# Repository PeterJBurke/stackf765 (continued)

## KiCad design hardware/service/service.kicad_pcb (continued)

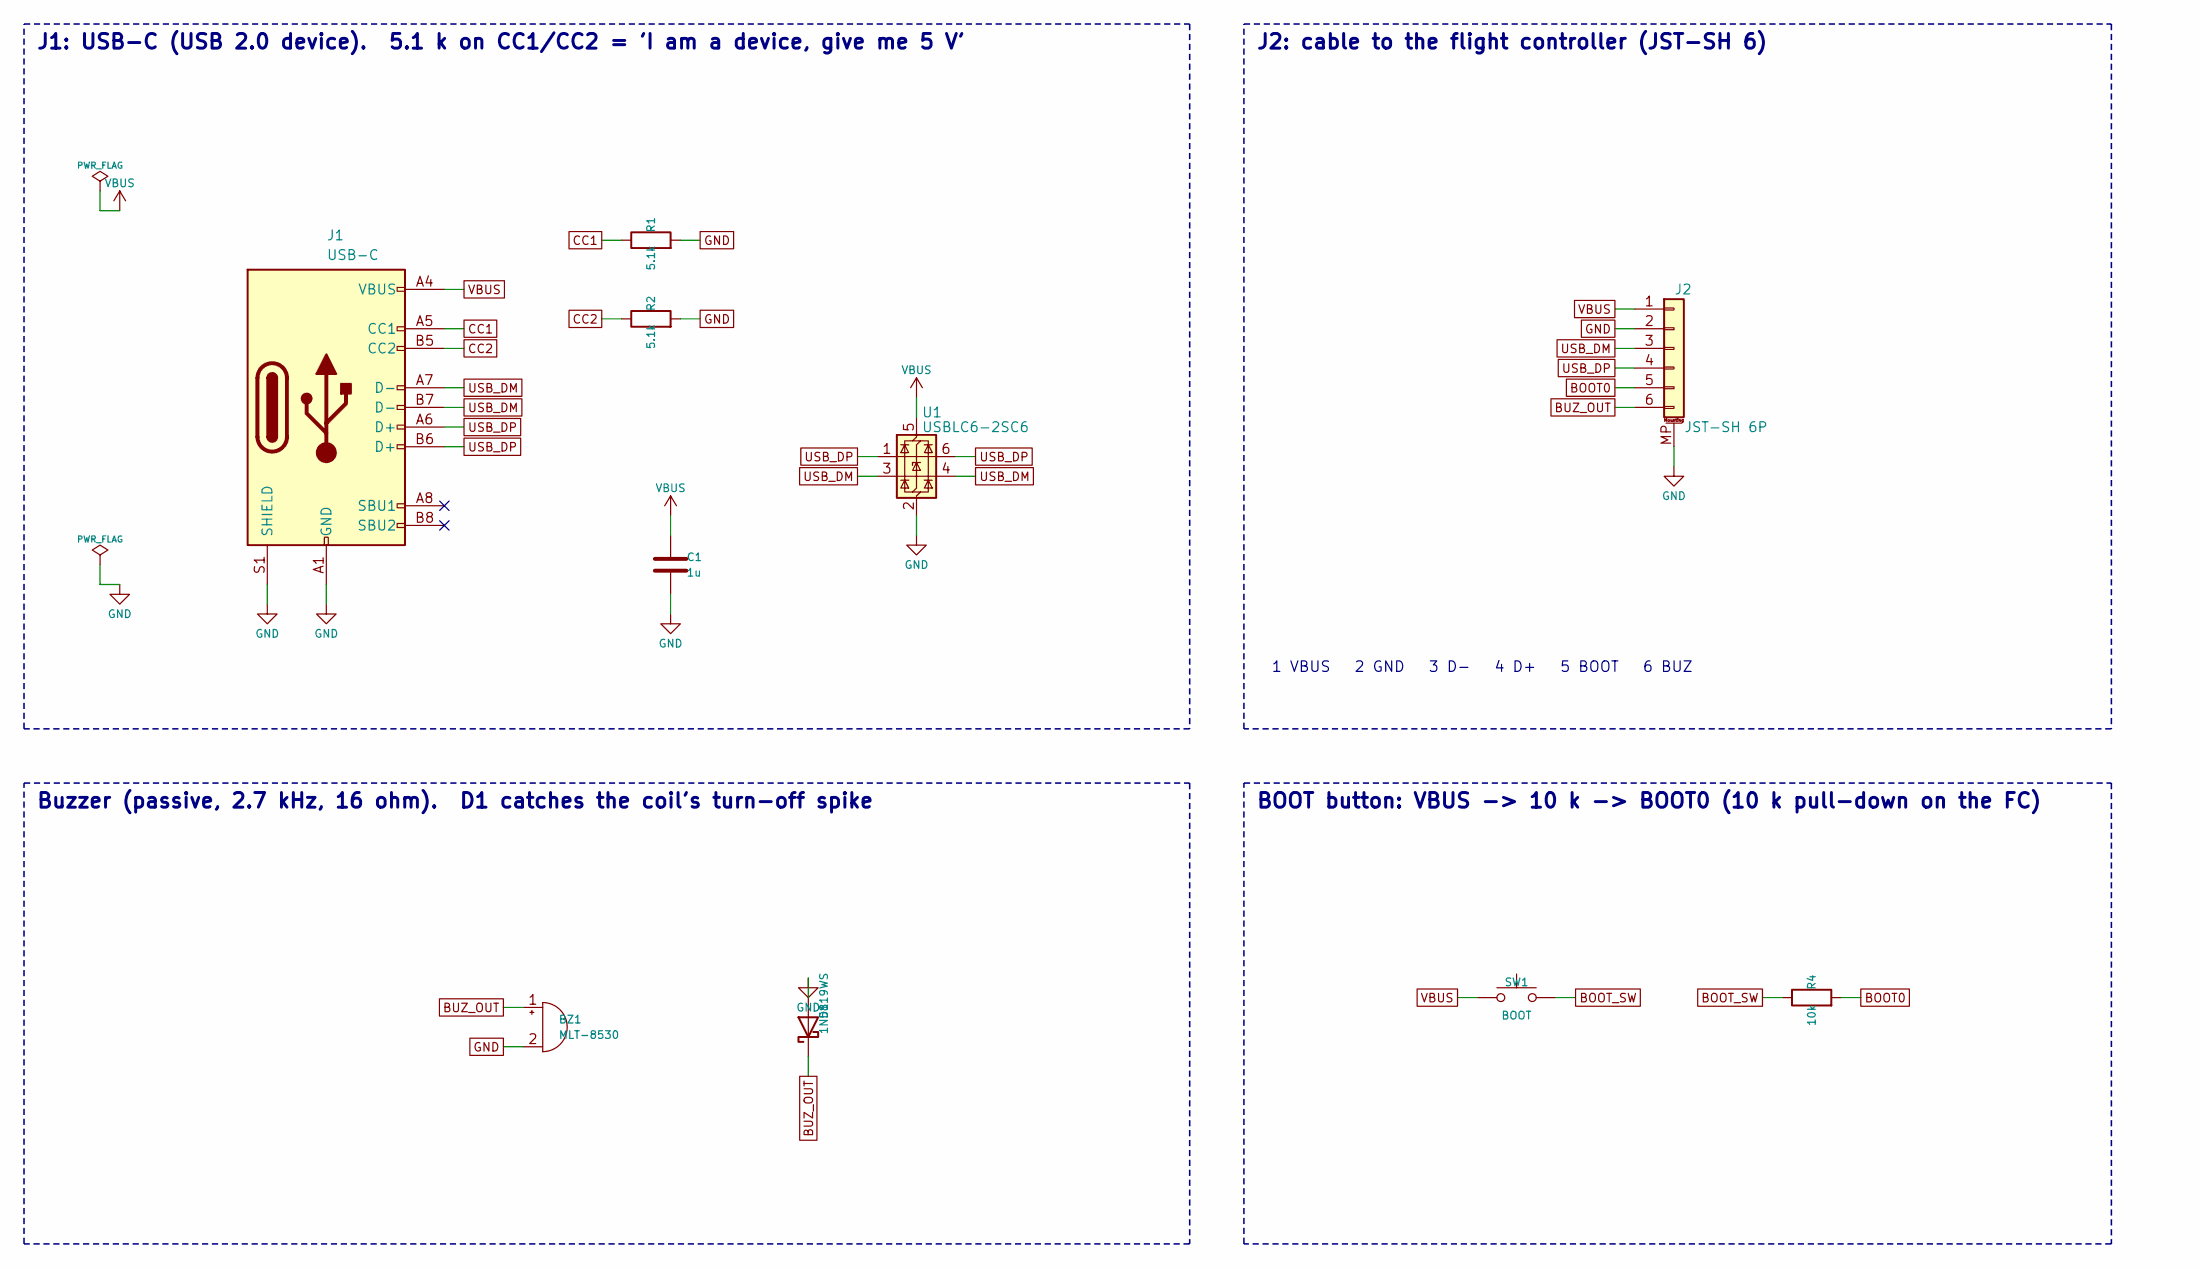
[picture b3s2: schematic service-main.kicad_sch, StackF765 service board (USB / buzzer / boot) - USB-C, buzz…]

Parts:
BZ1: MLT-8530; MagneticBuzzer_CUI_CMT-8504-100-SMT; MPN MLT-8530; LCSC C94599
C1: 1u; C_0402_1005Metric; MPN CL05A105KA5NQNC; LCSC C52923
D1: 1N5819WS; D_SOD-323; MPN 1N5819WS; LCSC C191023
J1: USB-C; USB_C_Receptacle_HRO_TYPE-C-31-M-12; MPN TYPE-C-31-M-12; LCSC C165948
J2: JST-SH 6P; JST_SH_SM06B-SRSS-TB_1x06-1MP_P1.00mm_Horizontal; MPN SM06B-SRSS-TB(LF)(SN); LCSC C160405
R1, R2: 5.1k; R_0402_1005Metric; MPN 0402WGF5101TCE; LCSC C25905
R4: 10k; R_0402_1005Metric; MPN 0402WGF1002TCE; LCSC C25744
SW1: BOOT; SW_Push_1P1T_XKB_TS-1187A; MPN TS-1187A-B-A-B; LCSC C318884
U1: USBLC6-2SC6; SOT-23-6; MPN USBLC6-2SC6; LCSC C7519

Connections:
BOOT0: J2.5, R4.2
BOOT_SW: R4.1, SW1.2
BUZ_OUT: BZ1.1 (+), D1.1 (K), J2.6
CC1: J1.A5 (CC1), R1.1
CC2: J1.B5 (CC2), R2.1
GND: BZ1.2 (-), C1.2, D1.2 (A), J1.A1 (GND), J1.A12 (GND), J1.B1 (GND), J1.B12 (GND), J1.S1 (SHIELD), J2.2, J2.MP (MountPin), R1.2, R2.2, U1.2 (GND)
USB_DM: J1.A7 (D-), J1.B7 (D-), J2.3, U1.3 (I/O2), U1.4 (I/O2)
USB_DP: J1.A6 (D+), J1.B6 (D+), J2.4, U1.1 (I/O1), U1.6 (I/O1)
VBUS: C1.1, J1.A4 (VBUS), J1.A9 (VBUS), J1.B4 (VBUS), J1.B9 (VBUS), J2.1, SW1.1, U1.5 (VBUS)

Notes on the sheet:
J1: USB-C (USB 2.0 device). 5.1 k on CC1/CC2 = 'I am a device, give me 5 V'
J2: cable to the flight controller (JST-SH 6)
1 VBUS 2 GND 3 D- 4 D+ 5 BOOT 6 BUZ
Buzzer (passive, 2.7 kHz, 16 ohm). D1 catches the coil's turn-off spike
BOOT button: VBUS -> 10 k -> BOOT0 (10 k pull-down on the FC)

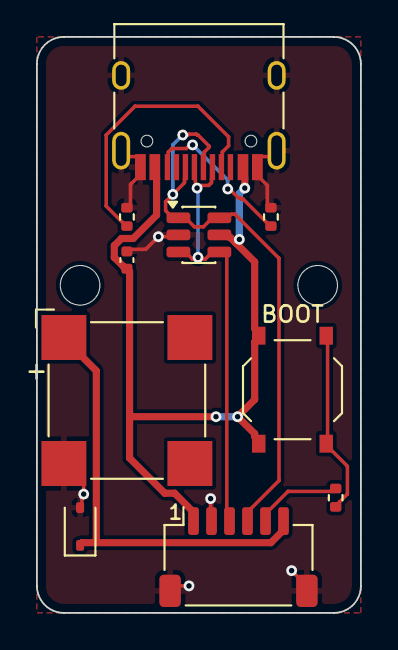
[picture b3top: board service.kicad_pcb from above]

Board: 2 copper layers, 18.0 x 32.0 mm, 12 parts (0 on the bottom side), 9 nets.

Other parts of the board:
H: (no value)
H#2: (no value)

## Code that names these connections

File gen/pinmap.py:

"""STM32F765VIT6 pin assignment: single table used by the schematic generator
and by tools/check_hwdef.py (which compares it with the ArduPilot hwdef.dat).

MCU pin -> (net name on the upper board, ArduPilot hwdef function label)
"""
PINMAP = {
    # USB + debug
    "PA11": ("USB_DM", "OTG_FS_DM"),
    "PA12": ("USB_DP", "OTG_FS_DP"),
    "PA13": ("SWDIO", "JTMS-SWDIO"),
    "PA14": ("SWCLK", "JTCK-SWCLK"),
    # UARTs (header labels TXn / RXn)
    "PA9":  ("TX1", "USART1_TX"), "PA10": ("RX1", "USART1_RX"),
    "PD5":  ("TX2", "USART2_TX"), "PD6":  ("RX2", "USART2_RX"),
    "PD8":  ("TX3", "USART3_TX"), "PD9":  ("RX3", "USART3_RX"),
    "PD1":  ("TX4", "UART4_TX"),  "PD0":  ("RX4", "UART4_RX"),
    "PC6":  ("TX6", "USART6_TX"), "PC7":  ("RX6", "USART6_RX"),
    "PE8":  ("TX7", "UART7_TX"),  "PE7":  ("RX7", "UART7_RX"),
    "PE1":  ("TX8", "UART8_TX"),  "PE0":  ("RX8", "UART8_RX"),
    # SPI1 - IMU
    "PA5": ("IMU_SCK", "SPI1_SCK"), "PA6": ("IMU_MISO", "SPI1_MISO"), "PA7": ("IMU_MOSI", "SPI1_MOSI"),
    "PC4": ("IMU_CS", "IMU1_CS"), "PC5": ("IMU_INT", "IMU1_INT"),
    # SPI2 - OSD
    "PB13": ("OSD_SCK", "SPI2_SCK"), "PB14": ("OSD_MISO", "SPI2_MISO"), "PB15": ("OSD_MOSI", "SPI2_MOSI"),
    "PB12": ("OSD_CS", "MAX7456_CS"),
    # I2C
    "PB6": ("SCL", "I2C1_SCL"), "PB7": ("SDA", "I2C1_SDA"),
    "PB10": ("BARO_SCL", "I2C2_SCL"), "PB11": ("BARO_SDA", "I2C2_SDA"),
    # analog
    "PC2": ("VBAT_ADC", "BATT_VOLTAGE_SENS"), "PC3": ("CURR_ADC", "BATT_CURRENT_SENS"),
    # LEDs, buzzer
    "PD10": ("LED_BLUE", "LED0"), "PD11": ("LED_GREEN", "LED1"),
    "PB9": ("BUZZER", "TIM11_CH1"),
    # outputs
    "PA0": ("M1", "TIM2_CH1"), "PA1": ("M2", "TIM2_CH2"), "PA2": ("M3", "TIM5_CH3"), "PA3": ("M4", "TIM5_CH4"),
    "PB0": ("M5", "TIM8_CH2N"), "PB1": ("M6", "TIM8_CH3N"),
    "PA8": ("LED_STRIP", "TIM1_CH1"),
    # microSD
    "PC8": ("SD_D0", "SDMMC_D0"), "PC9": ("SD_D1", "SDMMC_D1"), "PC10": ("SD_D2", "SDMMC_D2"),
    "PC11": ("SD_D3", "SDMMC_D3"), "PC12": ("SD_CK", "SDMMC_CK"), "PD2": ("SD_CMD", "SDMMC_CMD"),
}

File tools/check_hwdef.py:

#!/usr/bin/env python3
"""Cross-check the ArduPilot hwdef against the KiCad netlist of the upper board.

For every MCU pin it compares three independent sources:
  1. firmware/hwdef/StackF765/hwdef.dat   (what the firmware will drive)
  2. gen/pinmap.py                        (the design intent)
  3. the netlist KiCad extracts from hardware/upper/upper.kicad_sch (what was actually drawn)

and then follows each net to its destination (sensor pin, header pin, connector pin) and
checks that it is the expected one.  Exit status 0 = all consistent.

    python3 tools/check_hwdef.py
"""
import os
import re
import subprocess
import sys
import tempfile

ROOT = os.path.normpath(os.path.join(os.path.dirname(os.path.abspath(__file__)), ".."))
sys.path.insert(0, os.path.join(ROOT, "gen"))
from kigen.sexpr import parse, find, findall   # noqa: E402
from pinmap import PINMAP                      # noqa: E402

errors = []
rows = []


def err(msg):
    errors.append(msg)


# ---- 1. hwdef -------------------------------------------------------------------
hw = {}
for line in open(os.path.join(ROOT, "firmware/hwdef/StackF765/hwdef.dat")):
    line = line.split("#")[0].strip()
    m = re.match(r"^(P[A-K]\d+)\s+(\S+)\s+(\S+)", line)
    if m:
        hw[m.group(1)] = (m.group(2), m.group(3))

# ---- 3. netlist from the schematic -------------------------------------------------
tmp = tempfile.mkdtemp()
net = os.path.join(tmp, "upper.net")
subprocess.run(["kicad-cli", "sch", "export", "netlist", os.path.join(ROOT, "hardware/upper/upper.kicad_sch"),
                "-o", net], check=True, capture_output=True)
tree = parse(open(net).read())
pin_net = {}        # (ref, pin) -> net
net_nodes = {}      # net -> [(ref, pin, pinfunction)]
for n in findall(find(tree, "nets"), "net"):
    name = find(n, "name")[1].lstrip("/")
    for node in findall(n, "node"):
        ref, pin = find(node, "ref")[1], find(node, "pin")[1]
        fn = find(node, "pinfunction")
        pin_net[(ref, pin)] = name
        net_nodes.setdefault(name, []).append((ref, pin, fn[1] if fn else ""))

mcu_by_name = {}
for (ref, pin), name in pin_net.items():
    if ref == "U1":
        fn = next(f for r, p, f in net_nodes[name] if r == "U1" and p == pin)
        mcu_by_name[fn.split("/")[0]] = (pin, name)

# ---- compare hwdef <-> pinmap <-> schematic -----------------------------------------
for pin in sorted(set(hw) | set(PINMAP), key=lambda p: (p[1], int(p[2:]))):
    h = hw.get(pin)
    p = PINMAP.get(pin)
    s = mcu_by_name.get(pin, (None, None))
    if h is None:
        err(f"{pin}: in pinmap ({p[0]}) but not in hwdef.dat")
        continue
    if p is None:
        err(f"{pin}: in hwdef.dat ({h[0]}) but not in pinmap")
        continue
    if h[0] != p[1]:
        err(f"{pin}: hwdef function {h[0]} != pinmap {p[1]}")
    if s[1] != p[0]:
        err(f"{pin}: schematic net {s[1]} != pinmap net {p[0]}")
    others = [f"{r}.{q}" for r, q, f in net_nodes.get(s[1], []) if r != "U1"]
    rows.append((pin, s[0], h[0], s[1], ", ".join(sorted(others))))

# every connected MCU GPIO must be declared in hwdef
for name, (pin, netname) in mcu_by_name.items():
    if re.match(r"^P[A-K]\d+$", name) and not netname.startswith("unconnected-") and name not in hw \
            and name not in ("PH0", "PH1"):
        err(f"{name}: wired to {netname} in the schematic but missing from hwdef.dat")

# ---- destinations ---------------------------------------------------------------------
EXPECT = {   # net -> set of "REF.pin-function" that must be on it
    "IMU_SCK": {"U2.SCLK"}, "IMU_MOSI": {"U2.SDI"}, "IMU_MISO": {"U2.SDO"}, "IMU_CS": {"U2.CS"},
    "IMU_INT": {"U2.INT1"},
    "OSD_SCK": {"U4.SCLK"}, "OSD_MOSI": {"U4.SDIN"}, "OSD_MISO": {"U4.SDOUT"}, "OSD_CS": {"U4.~{CS}"},
    "BARO_SCL": {"U3.SCK"}, "BARO_SDA": {"U3.SDI"},
    "SD_D0": {"J4.DAT0"}, "SD_D1": {"J4.DAT1"}, "SD_D2": {"J4.DAT2"}, "SD_D3": {"J4.DAT3/CD"},
    "SD_CK": {"J4.CLK"}, "SD_CMD": {"J4.CMD"},
    "USB_DM": {"J5.Pin_3"}, "USB_DP": {"J5.Pin_4"},
    "VBAT_ADC": {"R14.2"}, "CURR_ADC": {"R15.2"}, "BUZZER": {"Q1.G"},
    "OSC_IN": {"Y1.1"}, "OSC_OUT": {"Y1.3"},
}
for i, r in enumerate("ABC"):
    pass
for netname, want in EXPECT.items():
    have = {f"{r}.{f or p}" for r, p, f in net_nodes.get(netname, [])} | \
           {f"{r}.{p}" for r, p, f in net_nodes.get(netname, [])}
    for w in want:
        if w not in have:
            err(f"net {netname}: expected node {w}, found {sorted(have)}")
# UART pins must reach the header pin carrying the same label
for netname, nodes in net_nodes.items():
    if re.match(r"^[TR]X\d$", netname) or netname in ("SDA", "SCL"):
        hdr = [f for r, p, f in nodes if r == "J1"]
        if len(hdr) != 1 or not hdr[0].replace("_", " ").endswith(" " + netname):
            err(f"net {netname}: header pin label mismatch {hdr}")

# motor and LED outputs must reach the signal pin (row A) of the rear-header column with the same label
for netname, label in [(f"M{i}", f"M{i}") for i in range(1, 7)] + [("LED_STRIP", "LED")]:
    hdr = [f for r, p, f in net_nodes.get(netname, []) if r == "J2"]
    if len(hdr) != 1 or not hdr[0].startswith("A") or not hdr[0].replace("_", " ").endswith(" " + label):
        err(f"net {netname}: rear header pin mismatch {hdr}")
    if any(r == "J3" for r, p, f in net_nodes.get(netname, [])):
        err(f"net {netname}: must not go to the board-to-board connector")

# I2C address / device strapping
def on(ref, func):
    return next((n for n, nodes in net_nodes.items() for r, p, f in nodes if r == ref and f == func), None)


if on("U3", "SDO") != "GND":
    err("BMP388 SDO is not tied to GND (hwdef expects I2C address 0x76)")
if on("U3", "CSB") != "+3V3_SENS":
    err("BMP388 CSB must be high for I2C mode")
if on("U2", "RESV7") != "GND":
    err("IMU pin 7 must be grounded")

print(f"{'MCU pin':8} {'pad':>4}  {'hwdef function':18} {'net':12} connects to")
for r in rows:
    print(f"{r[0]:8} {r[1]:>4}  {r[2]:18} {r[3]:12} {r[4]}")
print()
if errors:
    print(f"FAIL: {len(errors)} inconsistencies")
    for e in errors:
        print("  -", e)
    sys.exit(1)
print(f"PASS: {len(rows)} MCU pins consistent between hwdef.dat, pinmap.py and the KiCad schematic")
